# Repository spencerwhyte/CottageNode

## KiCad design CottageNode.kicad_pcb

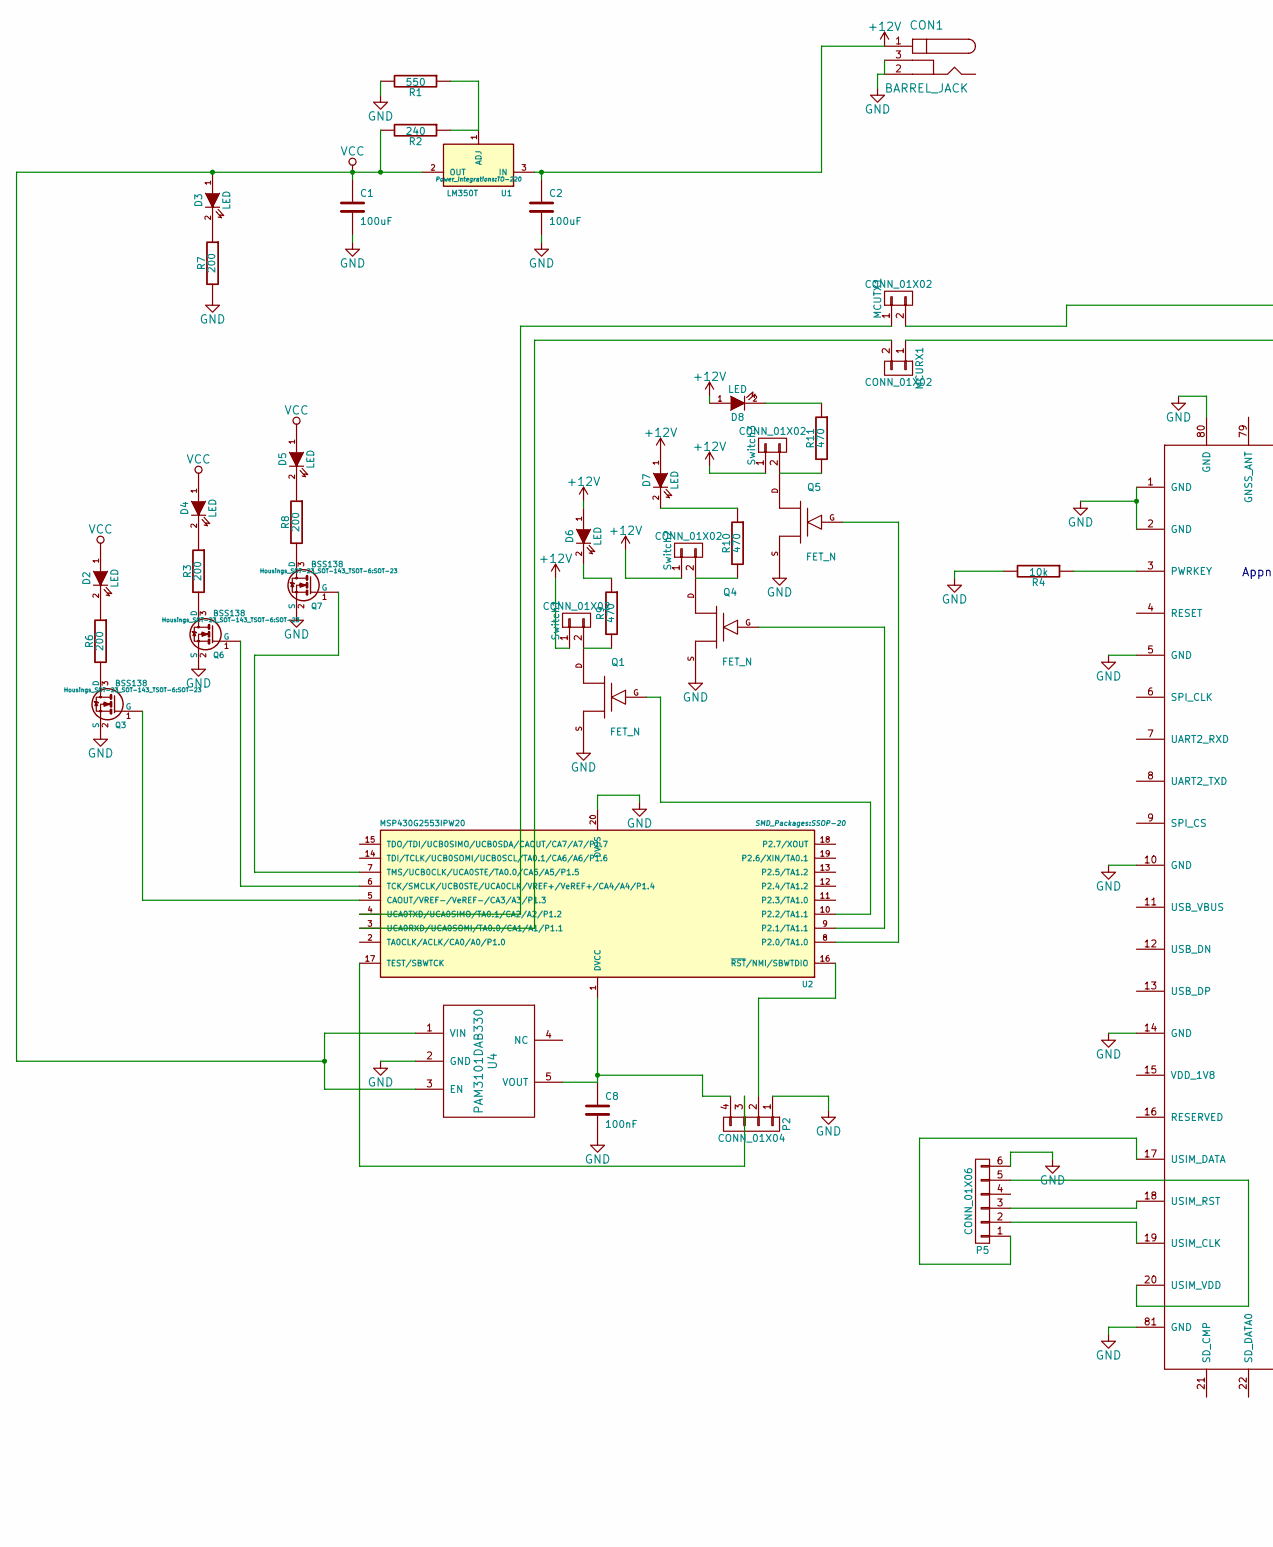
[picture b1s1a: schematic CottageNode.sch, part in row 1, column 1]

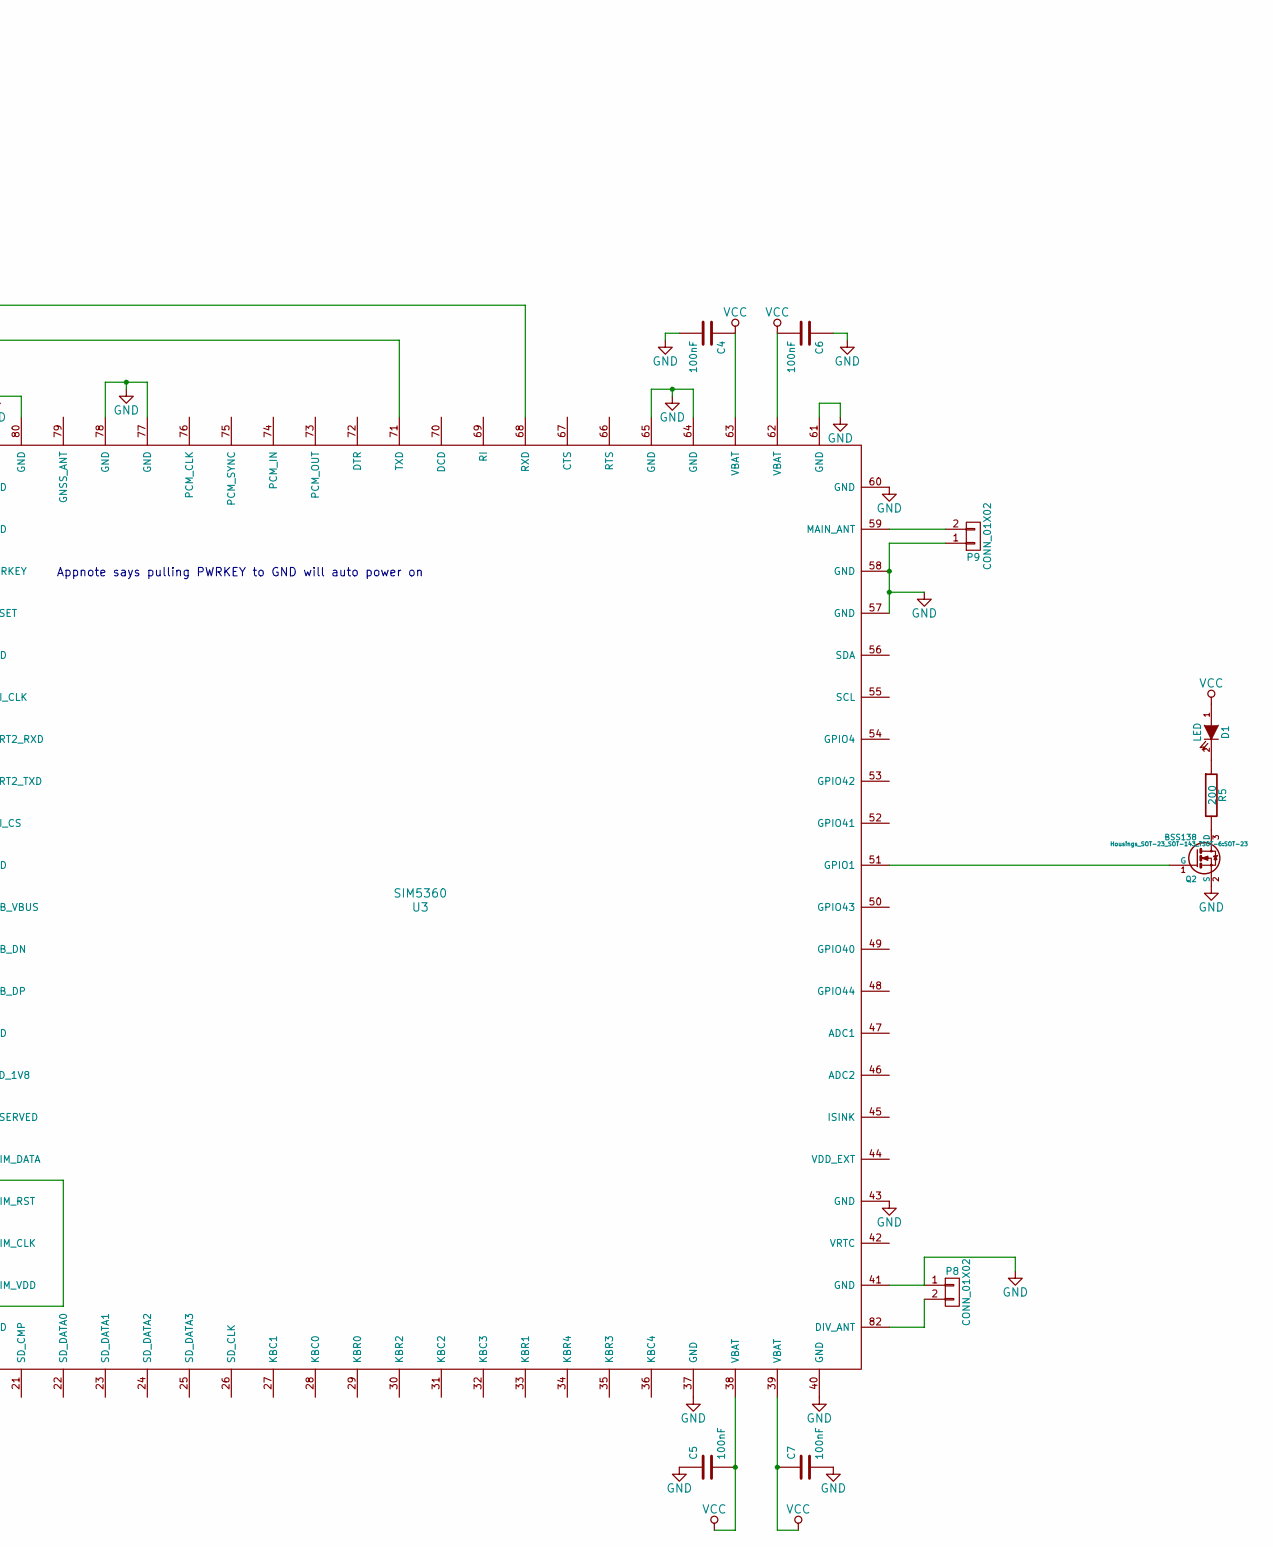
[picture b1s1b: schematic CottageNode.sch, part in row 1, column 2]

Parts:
C1, C2: 100uF; C_0805
C4, C5, C6, C7, C8: 100nF; C_0805
CON1: BARREL_JACK
D1, D2, D3, D4, D5, D6, D7, D8: LED; LED-0603
MCURX1: CONN_01X02; Pin_Header_Straight_1x02
MCUTX1: CONN_01X02; Pin_Header_Straight_1x02
P2: CONN_01X04; Pin_Header_Straight_1x04
P5: CONN_01X06; 693043020611
P8, P9: CONN_01X02; SMA_Right
Q1, Q4, Q5: FET_N; DPAK-3_GDS
Q2, Q3, Q6, Q7: BSS138; SOT-23
R1: 550; C_0805
R2: 240; C_0805
R3, R5, R6, R7, R8: 200; R_0603
R4: 10k; R_0402
R9, R10, R11: 470; R_0603
Switch1, Switch2, Switch3: CONN_01X02; AK300-2
U1: LM350T; TO-220
U2: MSP430G2553IPW20; SSOP-20
U3: SIM5360
U4: PAM3101DAB330; SOT-23-5

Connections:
+12V: C2.1, CON1.1, D6.1 (A), D7.1 (A), D8.1 (A), Switch1.1, Switch2.1, Switch3.1, U1.3 (IN)
GND: C1.2, C2.2, C4.2, C5.1, C6.1, C7.2, C8.2, CON1.2, CON1.3, P2.1, P5.6, P8.1, P9.1, Q1.S, Q2.2 (S), Q3.2 (S), Q4.S, Q5.S, Q6.2 (S), Q7.2 (S), R1.2, R4.2, R7.2, U2.20 (DVSS), U3.1 (GND), U3.2 (GND), U3.5 (GND), U3.10 (GND), U3.14 (GND), U3.37 (GND), U3.40 (GND), U3.41 (GND), U3.43 (GND), U3.57 (GND), U3.58 (GND), U3.60 (GND), U3.61 (GND), U3.64 (GND), U3.65 (GND), U3.77 (GND), U3.78 (GND), U3.80 (GND), U3.81 (GND), U4.2 (GND)
unnamed: C8.1, P2.4, U2.1 (DVCC), U4.5 (VOUT)
unnamed: D1.2 (K), R5.1
unnamed: D2.2 (K), R6.1
unnamed: D3.2 (K), R7.1
unnamed: D4.2 (K), R3.1
unnamed: D5.2 (K), R8.1
unnamed: D6.2 (K), R9.1
unnamed: D7.2 (K), R10.1
unnamed: D8.2 (K), R11.1
unnamed: MCURX1.1, U3.71 (TXD)
unnamed: MCURX1.2, U2.3 (UCA0RXD/UCA0SOMI/TA0.0/CA1/A1/P1.1)
unnamed: MCUTX1.1, U2.4 (UCA0TXD/UCA0SIMO/TA0.1/CA2/A2/P1.2)
unnamed: MCUTX1.2, U3.68 (RXD)
unnamed: P2.2, U2.16 (~RST~/NMI/SBWTDIO)
unnamed: P2.3, U2.17 (TEST/SBWTCK)
unnamed: P5.1, U3.17 (USIM_DATA)
unnamed: P5.2, U3.19 (USIM_CLK)
unnamed: P5.3, U3.18 (USIM_RST)
unnamed: P5.5, U3.20 (USIM_VDD)
unnamed: P8.2, U3.82 (DIV_ANT)
unnamed: P9.2, U3.59 (MAIN_ANT)
unnamed: Q1.D, R9.2, Switch1.2
unnamed: Q1.G, U2.10 (P2.2/TA1.1)
unnamed: Q2.1 (G), U3.51 (GPIO1)
unnamed: Q2.3 (D), R5.2
unnamed: Q3.1 (G), U2.5 (CAOUT/VREF-/VeREF-/CA3/A3/P1.3)
unnamed: Q3.3 (D), R6.2
unnamed: Q4.D, R10.2, Switch2.2
unnamed: Q4.G, U2.9 (P2.1/TA1.1)
unnamed: Q5.D, R11.2, Switch3.2
unnamed: Q5.G, U2.8 (P2.0/TA1.0)
unnamed: Q6.1 (G), U2.6 (TCK/SMCLK/UCB0STE/UCA0CLK/VREF+/VeREF+/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)
unnamed: Q6.3 (D), R3.2
unnamed: Q7.1 (G), U2.7 (TMS/UCB0CLK/UCA0STE/TA0.0/CA5/A5/P1.5)
unnamed: Q7.3 (D), R8.2
unnamed: R1.1, R2.1, U1.1 (ADJ)
unnamed: R4.1, U3.3 (PWRKEY)
VCC: C1.1, C4.1, C5.2, C6.2, C7.1, D1.1 (A), D2.1 (A), D3.1 (A), D4.1 (A), D5.1 (A), R2.2, U1.2 (OUT), U3.38 (VBAT), U3.39 (VBAT), U3.62 (VBAT), U3.63 (VBAT), U4.1 (VIN), U4.3 (EN)

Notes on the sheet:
Appnote says pulling PWRKEY to GND will auto power on

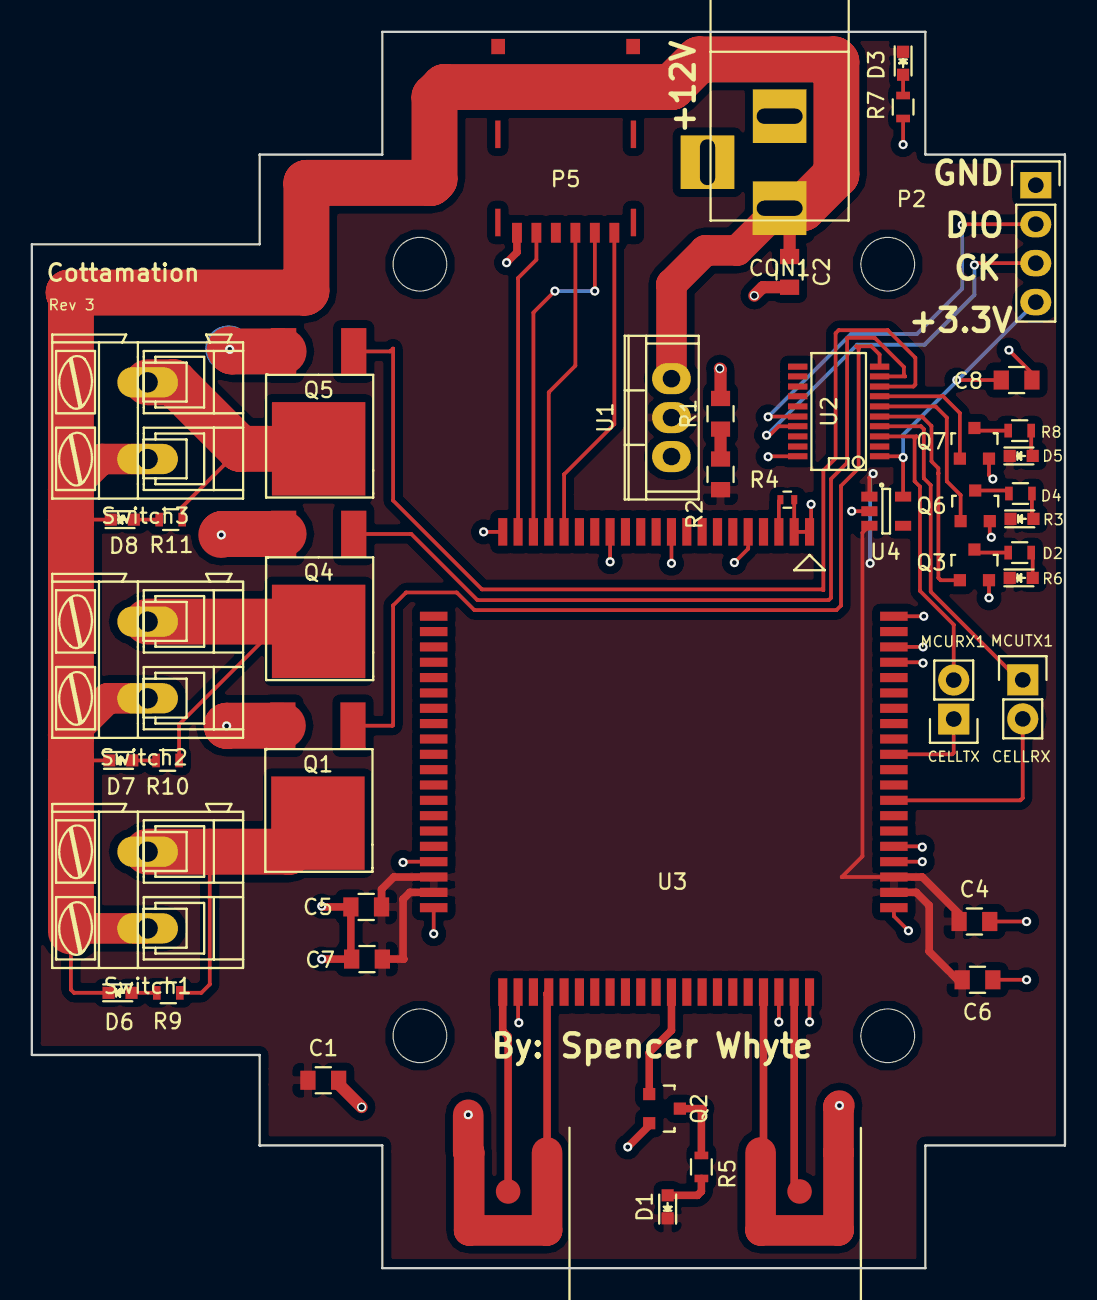
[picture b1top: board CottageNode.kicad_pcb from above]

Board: 2 copper layers, 67.4 x 80.6 mm, 47 parts (0 on the bottom side), 40 nets.

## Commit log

2018-11-23 Initial commit.
2018-11-23 Updating language
